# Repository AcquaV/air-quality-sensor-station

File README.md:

# ESP32-S3 Air Quality & Weather Station with 2.0" TFT Display

A compact, USB-C powered PCB for indoor air quality (IAQ) monitoring and a simple
barometric weather forecast, based on the **ESP32-S3**. It reads CO2, VOC/NOx,
temperature, humidity, pressure and (optionally) particulate matter, keeps time via
NTP, and shows everything on an external **2.0" IPS TFT** that wakes up on a
capacitive touch button.

---

## 🛠 Main Features

* **Microcontroller:** ESP32-S3-WROOM-1-N4 (2.4 GHz Wi-Fi + BLE 5.0, native USB).
* **Display:** external 2.0" IPS TFT LCD module, 240 x 320, ST7789 driver, 4-wire SPI.
  The module has **no backlight pin**, so it is switched on/off through its supply
  (see [Display Power Switch](#-display-power-switch)).
* **User input:** one separate capacitive touch button (TTP223 module, mounted on the
  enclosure): wakes the display after the timeout and switches screen.
* **Sensors (I2C):**
  * **SCD40 (Sensirion):** CO2, temperature, relative humidity.
  * **SGP41 (Sensirion):** VOC and NOx indices (uses SCD40 temperature/humidity for compensation).
  * **BMP580 (Bosch Sensortec):** barometric pressure, used for the weather forecast.
  * **SEN50 (Sensirion, optional):** PM1.0 / PM2.5 / PM4.0 / PM10 on a 6-pin JST GH connector.
* **Time:** NTP over Wi-Fi (no external RTC or crystal). Interval timing uses the
  ESP32 hardware timers.
* **Weather forecast:** short-term forecast from sea-level-corrected pressure and its
  3-hour trend (Zambretti-style algorithm, in firmware).
* **Power:** 5 V from USB-C, 3.3 V from an LDL1117S33R LDO, with input protection.

---

## ⚡ Power Supply Architecture

| Block | Part / value | Notes |
| :--- | :--- | :--- |
| Input | USB-C 16-pin receptacle, back side | CC1/CC2: 5.1 kΩ to GND (one each) |
| Surge protection | TVS **SMF5.0A** on VBUS, **before** the PTC | cathode to VBUS |
| Overcurrent | Resettable **PTC 0.75 A hold, 1812** | |
| Data-line ESD | **USBLC6-2SC6** (SOT-23-6) on USB_DATA+/- | next to the connector, short ground via; VBUS pin on the pre-PTC node |
| LDO | **LDL1117S33R** (ST), 3.3 V, 1.2 A, SOT-223 (LCSC `C435835`) | tab = VOUT (per ST datasheet) |
| Input caps | 10 µF + 100 nF, ceramic X5R/X7R, **16 V** | 10 µF in 0805 or larger |
| Output caps | 10 µF + 100 nF, ceramic X5R/X7R, **16 V** | LDL1117 is designed for ceramic output caps; keep ≥ 4.7 µF effective |
| Test points | 5V, 3V3, GND | |

**Thermal note:** the LDO dissipates (5 V − 3.3 V) x I (about 0.5 W at 300 mA). The tab
is **VOUT**, so it goes on a large **3V3** copper area (not GND), with thermal vias to a
3V3 area on another layer if you want to spread the heat.

---

## 📌 ESP32-S3 GPIO Mapping

| GPIO | Net label | Function | Notes |
| :---: | :--- | :--- | :--- |
| **IO0** | `IO0` | BOOT button (SW1) | 10 kΩ pull-up (R2), 100 nF debounce (C11) |
| **IO1** | `INT_PRESS` | BMP580 interrupt | optional |
| **IO4** | `TOUCH` | Capacitive button output (CN3) | 100 kΩ pull-down (R4) |
| **IO8** | `I2C_DATA` | I2C SDA | 2.2 kΩ pull-up (R5), test point TP6 |
| **IO9** | `I2C_CLK` | I2C SCL | 2.2 kΩ pull-up (R6), test point TP7 |
| **IO10** | `SCL_D` | TFT SPI clock (SCK) | |
| **IO11** | `SDA_D` | TFT SPI data (MOSI) | |
| **IO12** | `RST_D` | TFT reset | |
| **IO13** | `DC_D` | TFT data / command | |
| **IO14** | `CS_D` | TFT chip select | |
| **IO21** | `D_ENABLE` | TFT power switch control | active low, see [Display Power Switch](#-display-power-switch) |
| **IO19** | `USB_DATA-` | Native USB D- | |
| **IO20** | `USB_DATA+` | Native USB D+ | |
| **IO38** | | Status LED (LED1) | through 2.2 kΩ (R9), LED to GND |
| **EN** | | Reset button (SW2) | 10 kΩ pull-up (R1), 1 µF (C2) |

Unused GPIOs: `IO2`, `IO5`-`IO7`, `IO15`-`IO18`, `IO35`-`IO37`, `IO39`-`IO42`, `IO47`,
`IO48`. Avoid **IO3, IO45, IO46** (strapping pins).

---

## 🗺 I2C Address Map

All sensors share the 3.3 V I2C bus (`IO8` / `IO9`).

| Sensor | Measurements | Address | Notes |
| :--- | :--- | :---: | :--- |
| **BMP580** | Pressure & temperature | `0x47` | `SDO` and `CSB` pulled high to 3V3 |
| **SGP41** | VOC & NOx | `0x59` | Fixed |
| **SCD40** | CO2, temperature, humidity | `0x62` | Fixed |
| **SEN50** | Particulate matter | `0x69` | Fixed (`SEL` pin to GND = I2C mode) |

---

## 🔌 External Connectors

### 1. TFT display (CN2, 8 pins)

| Pin | Signal | ESP32-S3 |
| :---: | :--- | :--- |
| 1 | GND | GND |
| 2 | VCC | switched 3V3 (display supply, see below) |
| 3 | SCL | `IO10` (`SCL_D`) |
| 4 | SDA | `IO11` (`SDA_D`) |
| 5 | RST | `IO12` (`RST_D`) |
| 6 | DC | `IO13` (`DC_D`) |
| 7 | CS | `IO14` (`CS_D`) |
| 8 | NC | not connected |

The module header has 7 pins, read from left to right on the back of the module (header
at the top): CS, DC, RST, SDA, SCL, VCC, GND. Wire the cable so that **CN2 pin 1 (GND)
goes to the module's GND pin** and CN2 pin 7 (CS) to the module's CS pin, i.e. the order
is reversed with respect to the module. Check the labels printed on your module before
making the cable.

### 2. Capacitive touch button (CN3, 3 pins)

| Pin | Signal |
| :---: | :--- |
| 1 | GND |
| 2 | 3V3 |
| 3 | `TOUCH` (`IO4`, 100 kΩ pull-down) |

The TTP223 module is glued behind the enclosure wall (1-3 mm, no air gap). Check the
module's jumpers for active-high / momentary mode.

### 3. SEN50 particulate matter sensor (JST GH, 6-pin, 1.25 mm)

| Pin | SEN50 pin | PCB connection |
| :---: | :--- | :--- |
| 1 | VDD | `+5V` (after the PTC, with a local 10 µF) |
| 2 | GND | `GND` |
| 3 | SDA | `IO8` |
| 4 | SCL | `IO9` |
| 5 | SEL | `GND` (forces I2C) |
| 6 | NC | not connected |

---

## 🖥 Display Power Switch

The TFT module has no backlight pin: its backlight is on whenever the module is powered.
To turn the display off after the timeout, the module supply is switched by a high-side
**P-MOSFET** (Q1, AO3401A, SOT-23, LCSC `C15127`).

| Part | Value | Function |
| :--- | :--- | :--- |
| Q1 | AO3401A | source on 3V3, drain on the display supply |
| R11 | 10 kΩ | in series from `D_ENABLE` (`IO21`) to the gate |
| R10 | 100 kΩ | pull-up from `D_ENABLE` to 3V3: display off at boot / reset |
| C17 | 100 nF | gate to 3V3 (source): soft start with R11 (about 1 ms) |
| C12 + C16 | 10 µF + 100 nF | decoupling on the display supply, next to CN2 |
| Discharge | 2 x 100 kΩ in parallel (50 kΩ) | across C12/C16: discharges the display supply when off |

`D_ENABLE` low = display on, high or high-impedance = display off. The soft start limits
the inrush current into the module capacitors, which would otherwise dip the 3V3 rail
and could reset the ESP32.

Firmware notes:
* The TFT must be **re-initialized after every power-up**: set `D_ENABLE` low, wait
  20-50 ms, re-enable the SPI pins, pulse `RST_D` low for about 10 ms, wait about 120 ms,
  then run the driver init. Drivers that initialize the display once at boot (such as
  ESPHome's built-in display component) are not ideal with power gating; an Arduino
  sketch with LovyanGFX or TFT_eSPI is easier.
* Before switching the display off, drive `CS_D`, `DC_D`, `RST_D`, `SDA_D` and `SCL_D`
  **low** (or set them as inputs), so the module is not back-powered through its signal
  pins.
* Touch behaviour: a short touch wakes the display when it is off, or changes screen
  when it is on; an inactivity timeout (for example 30-60 s) switches it off again.

---

## 📊 Power Budget (estimates)

| Load | Typical | Notes |
| :--- | :--- | :--- |
| ESP32-S3 | ~0.1 A, Wi-Fi peaks up to ~0.5 A | |
| TFT (backlight on) | 25-80 mA | depends on the module; measure it |
| TFT (off) | ~0 | via the P-MOSFET |
| Sensors | ~20 mA | |
| SEN50 | ~60-70 mA at 5 V | optional |

The LDO is 1.2 A, so there is plenty of margin. Heat is set by (5 V − 3.3 V) x I.

---

## 🌦 Weather Forecast

The pressure measured by the BMP580 is corrected to sea level using your altitude and
compared over time. The 3-hour trend selects a forecast text (rising: improving,
falling: worsening, steady: unchanged). The pressure history is kept in flash so it
survives power loss (see [Pressure History in Flash](#-pressure-history-in-flash)).

Place the BMP580 and SCD40 **away from the LDO and from the TFT**, and consider a PCB
slot between them: self-heating biases temperature and humidity.

---

## 💾 Pressure History in Flash

The 3-hour pressure trend needs a history that must survive a reboot or a power loss.
It is stored in the 4 MB flash of the module (NVS or LittleFS); the amount of data is
tiny.

| Item | Choice |
| :--- | :--- |
| Storage | NVS (key-value, with wear levelling) or LittleFS |
| Data | Circular buffer of samples: `{unix timestamp, raw pressure}` (a few bytes each) |
| Sampling | One sample every 10-15 min, keep the last 6 h (about 24-36 samples) |
| Flash writes | Samples are kept in RAM and the buffer is written to flash every 30 min |
| What is stored | **Raw** sensor pressure (the sea-level correction is applied when reading) |

**Boot sequence**
1. Wait for the NTP time sync (timestamps are only valid after it).
2. Load the buffer from flash.
3. Discard samples that are too old (e.g. older than 6 h) or have an invalid timestamp.
4. If at least 3 h of valid history remain, the trend and the forecast are available
   immediately; otherwise they are shown after the history has been rebuilt.

**Notes**
* **Wear:** one write every 30 min is about 17,500 writes per year. NOR flash is
  typically rated for around 100,000 erase cycles per sector (check the flash datasheet
  of your module) and NVS spreads the writes over several sectors, so wear is not a
  practical concern. Do **not** write to flash at every measurement.
* **Power loss:** without a battery-backed RTC, the samples taken since the last flash
  write (at most 30 min) are lost.
* **No timestamp, no sample:** do not store samples before the time is synchronized.

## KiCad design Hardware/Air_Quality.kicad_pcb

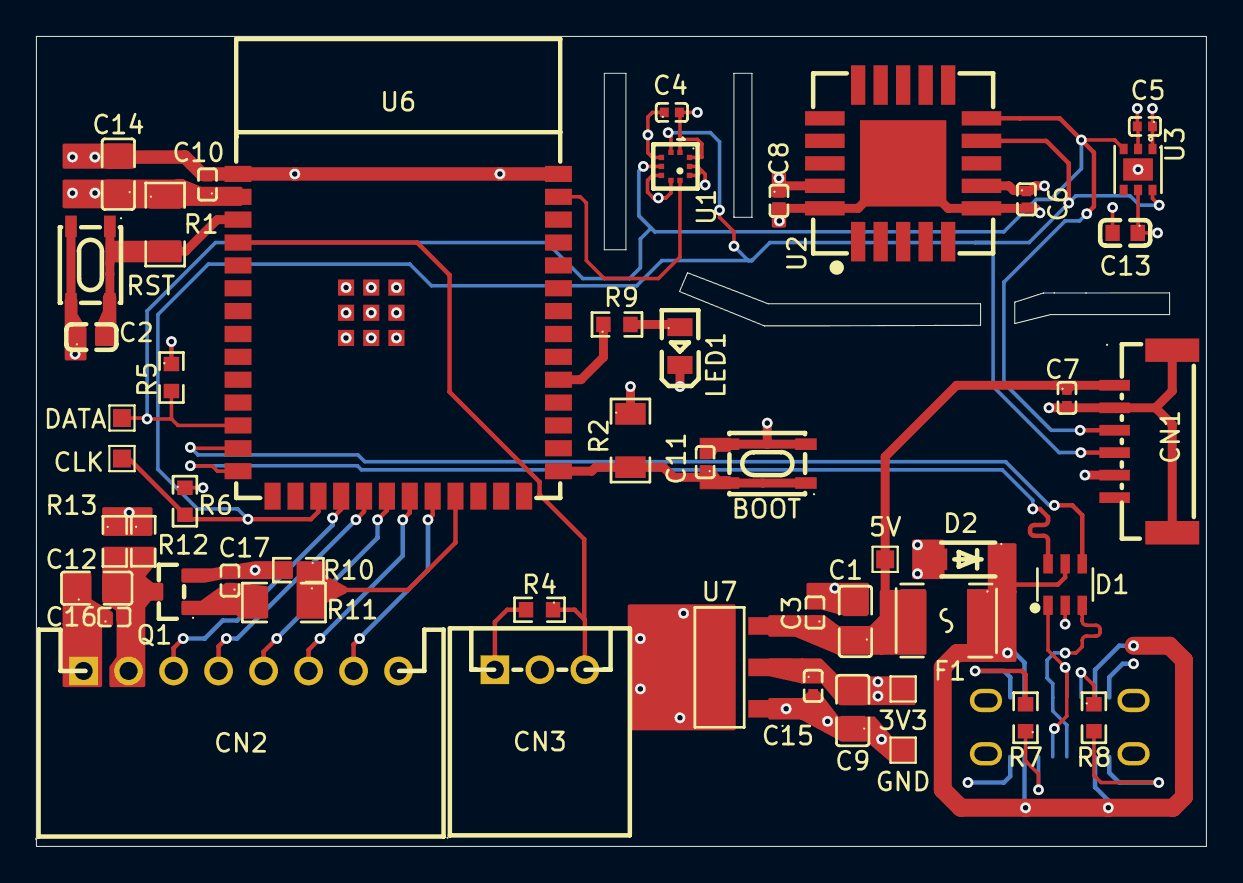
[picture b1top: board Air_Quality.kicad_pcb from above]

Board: 4 copper layers, 65.0 x 45.0 mm, 50 parts (1 on the bottom side), 26 nets.

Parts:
3V3, 5V: TestPoint_Alt; TestPoint_Pad_1.0x1.0mm
BOOT: BOOT; C55200589_SW-SMD_4P-L4_2-W3_4-P2_15-LS5_2
C1, C9, C12, C14: 10uF; C1713_C0805
C2, C13: 1uF; C1592_C0603
C3, C4, C5, C6, C7, C8, C10, C11, C15, C16, C17: 100nF; C1525_C0402
CLK: TestPoint_Alt; TestPoint_Pad_1.0x1.0mm
CN1: A1257WR-S-6P; C225129_CONN-SMD_A1257WR-S-6P
CN2: TFT DISPLAY; C157914_CONN-TH_S8B-XH-A-LF-SN
CN3: CAPACITIVE BUTTON; C157928_CONN-TH_S3B-XH-A-LF-SN
D1: USBLC6-2SC6; C7519_SOT-23-6_L2_9-W1_6-P0_95-LS2_8-BL
D2: SMF5.0A; C169426_SOD-123F_L2_8-W1_8-LS3_7-RD
DATA: TestPoint_Alt; TestPoint_Pad_1.0x1.0mm
F1: 0.75A; C20996_F1812
GND: TestPoint_Alt; TestPoint_Pad_1.0x1.0mm
LED1: XL-0805QBC; C2293_LED0805-R-RD
Q1: AO3401A; C15127_SOT-23_L2_9-W1_3-P1_90-LS2_4-BR
R1, R2, R11: 10K; C17902_R1206
R4, R10, R12, R13: 100k; C14675_R0603
R5, R6, R9: 2.2K; C4190_R0603
R7, R8: 5.1K; C23186_R0603
RST: RESET; C55200589_SW-SMD_4P-L4_2-W3_4-P2_15-LS5_2
U1: BMP580; C22391138_LGA-10_L2_0-W2_0-P0_50-TL_BMP580
U2: SCD40-D-R1; C3037696_LGA-20_L10_1-W10_1-P1_25-TL
U3: SGP41-D-R4; C3659325_DFN-6_L2_4-W2_4-P0_80-TL-EP
U6: ESP32-S3-WROOM-1-N4; C2913197_WIFIM-SMD_ESP32-S3-WROOM-1-N8
U7: LDL1117S33R; C435835_SOT-223-4_L6_5-W3_5-P2_30-LS7_0-BR
USB1: HYCW395-USBC16-085B; C5338274_USB-C-SMD_HYCW395-USBC16-085B

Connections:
3V3: 3V3.1 (1_1), C4.2, C5.1, C6.1, C8.1, C9.2, C10.1, C13.1, C14.1, C15.1, C17.2, CN3.2 (3V3), Q1.2 (S), R1.1, R2.1, R5.1, R6.1, R10.2, U1.1 (VDDIO), U1.5 (SDO), U1.6 (CSB), U1.10 (VDD), U2.7 (VDD), U2.19 (VDDH), U3.1 (VDD), U3.5 (VDDH), U6.2 (3V3), U7.2 (VOUT), U7.4 (VOUT)
5V: 5V.1 (1_1), C1.1, C3.1, C7.1, CN1.1 (VCC), F1.2, U7.3 (VIN)
CS_D: CN2.7 (CS), U6.22 (IO14)
DC_D: CN2.6 (DC), U6.21 (IO13)
D_ENABLE: R10.1, R11.1, U6.23 (IO21)
GND: BOOT.3, BOOT.4, C1.2, C2.1, C3.2, C4.1, C5.2, C6.2, C7.2, C8.2, C9.1, C10.2, C11.2, C12.1, C13.2, C14.2, C15.2, C16.1, CN1.2 (GND), CN1.5 (SEL), CN1.7, CN1.8, CN2.1 (GND), CN3.1 (GND), D1.2, D2.2, GND.1 (1_1), LED1.2 (K), R4.2, R7.2, R8.2, R12.1, R13.1, RST.3, RST.4, U1.3 (VSS), U1.8 (VSS), U1.9 (VSS), U2.6 (GND), U2.20 (GND), U2.21 (GND), U3.2 (VSS), U3.7 (EP), U6.1 (GND), U6.40 (GND), U6.41 (GND), U7.1 (GND), USB1.1 (EH), USB1.A1 (GND), USB1.A12 (GND), USB1.B1 (GND), USB1.B12 (GND)
I2C_CLK: CLK.1 (1_1), CN1.4 (SCL), R6.2, U1.2 (SCK), U2.9 (SCL), U3.6 (SCL), U6.17 (IO9)
I2C_DATA: CN1.3 (SDA), DATA.1 (1_1), R5.2, U1.4 (SDI), U2.10 (SDA), U3.3 (SDA), U6.12 (IO8)
INT_PRESS: U1.7 (INT), U6.39 (IO1)
unnamed: C12.2, C16.2, CN2.2 (VCC), Q1.3 (D), R12.2, R13.2
unnamed: D1.5, D2.1, F1.1, USB1.A4 (VBUS), USB1.A9 (VBUS), USB1.B4 (VBUS), USB1.B9 (VBUS)
unnamed: LED1.1 (A), R9.2
unnamed: C17.1, Q1.1 (G), R11.2
unnamed: C2.2, R1.2, RST.1, RST.2, U6.3 (EN)
unnamed: BOOT.1, BOOT.2, C11.1, R2.2, U6.27 (IO0)
unnamed: R9.1, U6.31 (IO38)
unnamed: R8.1, USB1.A5 (CC1)
unnamed: R7.1, USB1.B5 (CC2)
unnamed: D1.3, USB1.A7 (Dn1), USB1.B7 (Dn2)
unnamed: D1.1, USB1.A6 (Dp1), USB1.B6 (Dp2)
RST_D: CN2.5 (RST), U6.20 (IO12)
SCL_D: CN2.3 (SCL), U6.18 (IO10)
SDA_D: CN2.4 (SDA), U6.19 (IO11)
TOUCH: CN3.3 (TOUCH), R4.1, U6.4 (IO4)
USB_DATA+: D1.6, U6.14 (IO20)
USB_DATA-: D1.4, U6.13 (IO19)
